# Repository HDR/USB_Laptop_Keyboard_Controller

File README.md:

# USB Teensy T61 Controller

Based on [thedalles77](https://github.com/thedalles77/)'s version just smaller

## BOM

| Reference        | Part Number           | Description  |
| ------------- |:-------------:| -----:|
| J1 | 0543630489 | 40 Pin FPC keyboard connector (Or pull off a scrap board) |
| U1 | Teensy LC |  |                               
| U2 | TLV810MDBZR | 4.38 Volt Reset Generator SOT23 |
| Q1 | BSS138 | NFET SOT23 |
| Q2 | BSS138 | NFET SOT23 |
| R1 | ERJ-PA3J103V | 0603 10K Resistor |
| R2 | ERJ-PA3J103V | 0603 10K Resistor |
| R3 | ERJ-PA3J103V | 0603 10K Resistor |
| R4 | ERJ-PA3J103V | 0603 10K Resistor |
| C1 | 06035C104KAT2A | 0603 0.1uF Capacitor |
| C2 | 06035C104KAT2A | 0603 0.1uF Capacitor |

## Images

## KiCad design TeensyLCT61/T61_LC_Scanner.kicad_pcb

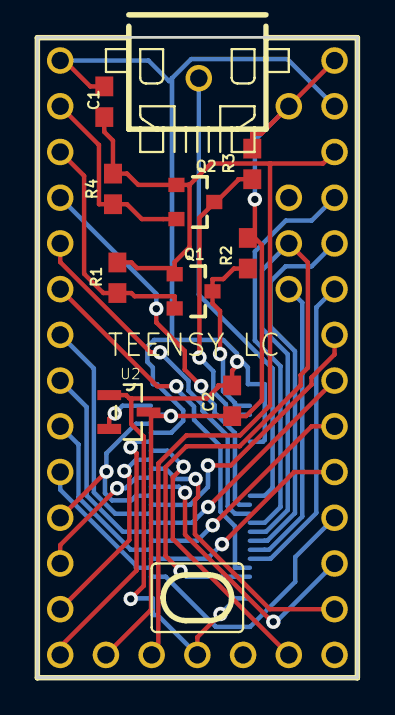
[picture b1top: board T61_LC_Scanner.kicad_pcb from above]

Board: 2 copper layers, 17.8 x 35.6 mm, 12 parts (0 on the bottom side), 33 nets.

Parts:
C1, C2: 0.1uF; 0603
J1: WM6787CT-ND
PWR: TestPoint_THTPad_D1.5mm_Drill0.7mm
Q1, Q2: 220mA/50V/3.5Ω; SOT23-3
R1, R2, R3, R4: 10k; 0603
U1: TEENSY_LC
U2: TLV810SDBZT; SOT95P237X112-3N

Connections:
unnamed: C1.1, Q1.1, Q2.1, R1.2, R4.2, U1.3V1, U1.3V2
unnamed: C1.2, C2.2, J1.P$31, J1.P$34, J1.P$41, J1.P$42, J1.P$43, J1.P$44, U1.GND1, U1.GND2, U1.GND3, U2.1
unnamed: C2.1, J1.P$38, R2.2, R3.2, U1.5V, U1.VIN, U1.VUSB, U2.3
unnamed: J1.P$1, J1.P$11, U1.24
unnamed: J1.P$2, U1.16
unnamed: J1.P$3, U1.4
unnamed: J1.P$4, U1.8
unnamed: J1.P$5, U1.21
unnamed: J1.P$6, U1.17
unnamed: J1.P$7, U1.25
unnamed: J1.P$8, U1.7
unnamed: J1.P$9, U1.22
unnamed: J1.P$10, U1.18
unnamed: J1.P$12, U1.6
unnamed: J1.P$13, U1.23
unnamed: J1.P$14, U1.19
unnamed: J1.P$15, U1.3
unnamed: J1.P$16, U1.5
unnamed: J1.P$17, U1.2
unnamed: J1.P$18, U1.20
unnamed: J1.P$19, PWR.1
unnamed: J1.P$20, J1.P$36, U1.9
unnamed: J1.P$22, U1.15
unnamed: J1.P$24, U1.10
unnamed: J1.P$26, U1.14
unnamed: J1.P$28, U1.11
unnamed: J1.P$30, U1.26
unnamed: J1.P$32, U1.12
unnamed: J1.P$37, Q2.3, R3.1
unnamed: J1.P$39, Q1.3, R2.1
unnamed: J1.P$40, U2.2
unnamed: Q1.2, R1.1, U1.1
unnamed: Q2.2, R4.1, U1.0

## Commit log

2019-10-02 init
